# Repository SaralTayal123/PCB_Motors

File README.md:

# PCB_Motors
Code &amp; Firmware to generate continuous coil PCB motor designs

Bare PCB Pictures: 

Completed Dual PCB Stator, center rotor motor

## Media

Videos of the motor spinning and build pictures are in the Media folder

## Cloning the repo
Note that if you clone the repo, you will also need to intialize the submodules. You can do so as follows

```
git clone git@github.com:SaralTayal123/PCB_Motors.git
cd PCB_Motors

git submodule init
git submodule update
```

You will also need to delete/comment out line 6 of `kicad-coil-plugins/pcb_json.py` as follows

```
import json
import pandas as pd
import numpy as np
import matplotlib.pyplot as plt

# from helpers import rotate ### Modify by commenting out ###
```

## How to build your own motors

Option 1 *(Suggested)*: Simply use the existing kicad design and order the current designed version through a manufacturer like PCBway.

Option 2: Design your own PCB motors using the python script. Steps for that are outlined below

### Step 1: 
 
Calculate the appropriate winding pattern. Using the following link, find a slot-magnet combo that will produce a repeating pattern of "A", "B", "C". The ABC phases can be in any order and any case (upper or lower) as long as the pattern that they appear in are consistant. The other restriction is that your Slot number needs to be a multiple of 6 given this winding pattern. For example, I used a 36 slot, 12 magnet pole design and achieved a pattern of "AbC" as pictured below. The upper/lower case refers to the polarity of the coil phase and can be easily switched during wiring, which is why it's not case sensitive as long as the pattern is repeated. 

Calculator link: https://www.bavaria-direct.co.za/scheme/calculator/

This step can be a little tedious since you will need to find magnets that will fit your motor inner/outer diameter while matching the pole pole pair count. If you need more flexibility on not requiring slots be a multiple of 6, or follow a different winding pattern, then this wave motor design isn't the best option for you, and a traditional repeated coil design like this is ideal for you: https://github.com/atomic14/kicad-coil-plugins/tree/216a77b6a4d9532b090e98a6620eb1c3f18db77d

### Step 2: Use the python script

Using the slot/pole combo from step 1 (or using the reccomended 36/12 design), open the continous_coil_gen.ipynb python notebook. Here, input the inner and outer diameter of your coils. You should tailor these to be the width of your magnets to make your motor as effective aas possible. You can also tune a few PCB trace parameters here depending on the capabilities of the PCB manufacturing available to you

### Step 3: Import the Kicad coil design into Kicad

Using the [tool here](https://github.com/atomic14/kicad-coil-plugins/tree/216a77b6a4d9532b090e98a6620eb1c3f18db77d), import your coil design into kicad. If you decide to work with my example board design in KiCad, you should right click the imported coil and move it to the origin to center it perfectly for your design.

Finally, integrate your coils with the rest of the motor controller circuitry to create your own PCB Motor!

## BOM for the example motor
Simple BOM, Cost is ~$25 + shipping
PCBWAY cost ~$26 for 5 boards + Shipping
Magnets 24 pieces @ $0.37 each = $30 (I recommend some spares as they tend to snap/break if they fly out of your hand into a metal object) : https://www.magnet4less.com/neodymium-bar-magnets-1-2-in-x-1-4-in-x-1-8-in-n42

### Rough Specs

Configuration: 2 sided PCB Stator, Rotor in the middle, 8V, Star wiring pattern

Stall torque: 0.008 Nm
Top Speed: 170 Rad/s
Max Power draw: 5 Watts
Peak output power (measured torque x angular velocity): 0.3 Watts

### Testing

Motor charecterization was performed by using 3d printed disc with bolts to serve as a known inertial load to our motor. Measuring the angular acceleration at a full torque command at each angular velocity allowed us to charecterize the torque curve of the motor and the output power curve for the motor (pictured above). This sort of testing is commonnly used for testing cars and is called an inertial dyno. The extra inertial load attached to the PCB motor is pictured below.

The neat thing about using this test is that all one needed to do was add some extra data-logging firmware, and the PCB motors can self-charecterize themselves without any external equipment!

We were also able to monitor a DC Amp-meter on the input power line of the motor to measure system efficiency, howerver there was a lot of switching noise on that power rail to measure a clean signal. Noisy graph is available in Media/torq_eff.png image. The efficiency test needs to be repeated with a low pass filter and a secondary means to test the motor with the motor controller out of the loop. 

### TODO: 
* Why this design
* Star vs Delta wiring
* How to pick winding factor and why conventional winding table won't work

Motor winding image credits: 
https://www.bavaria-direct.co.za/info/#prettyPhoto

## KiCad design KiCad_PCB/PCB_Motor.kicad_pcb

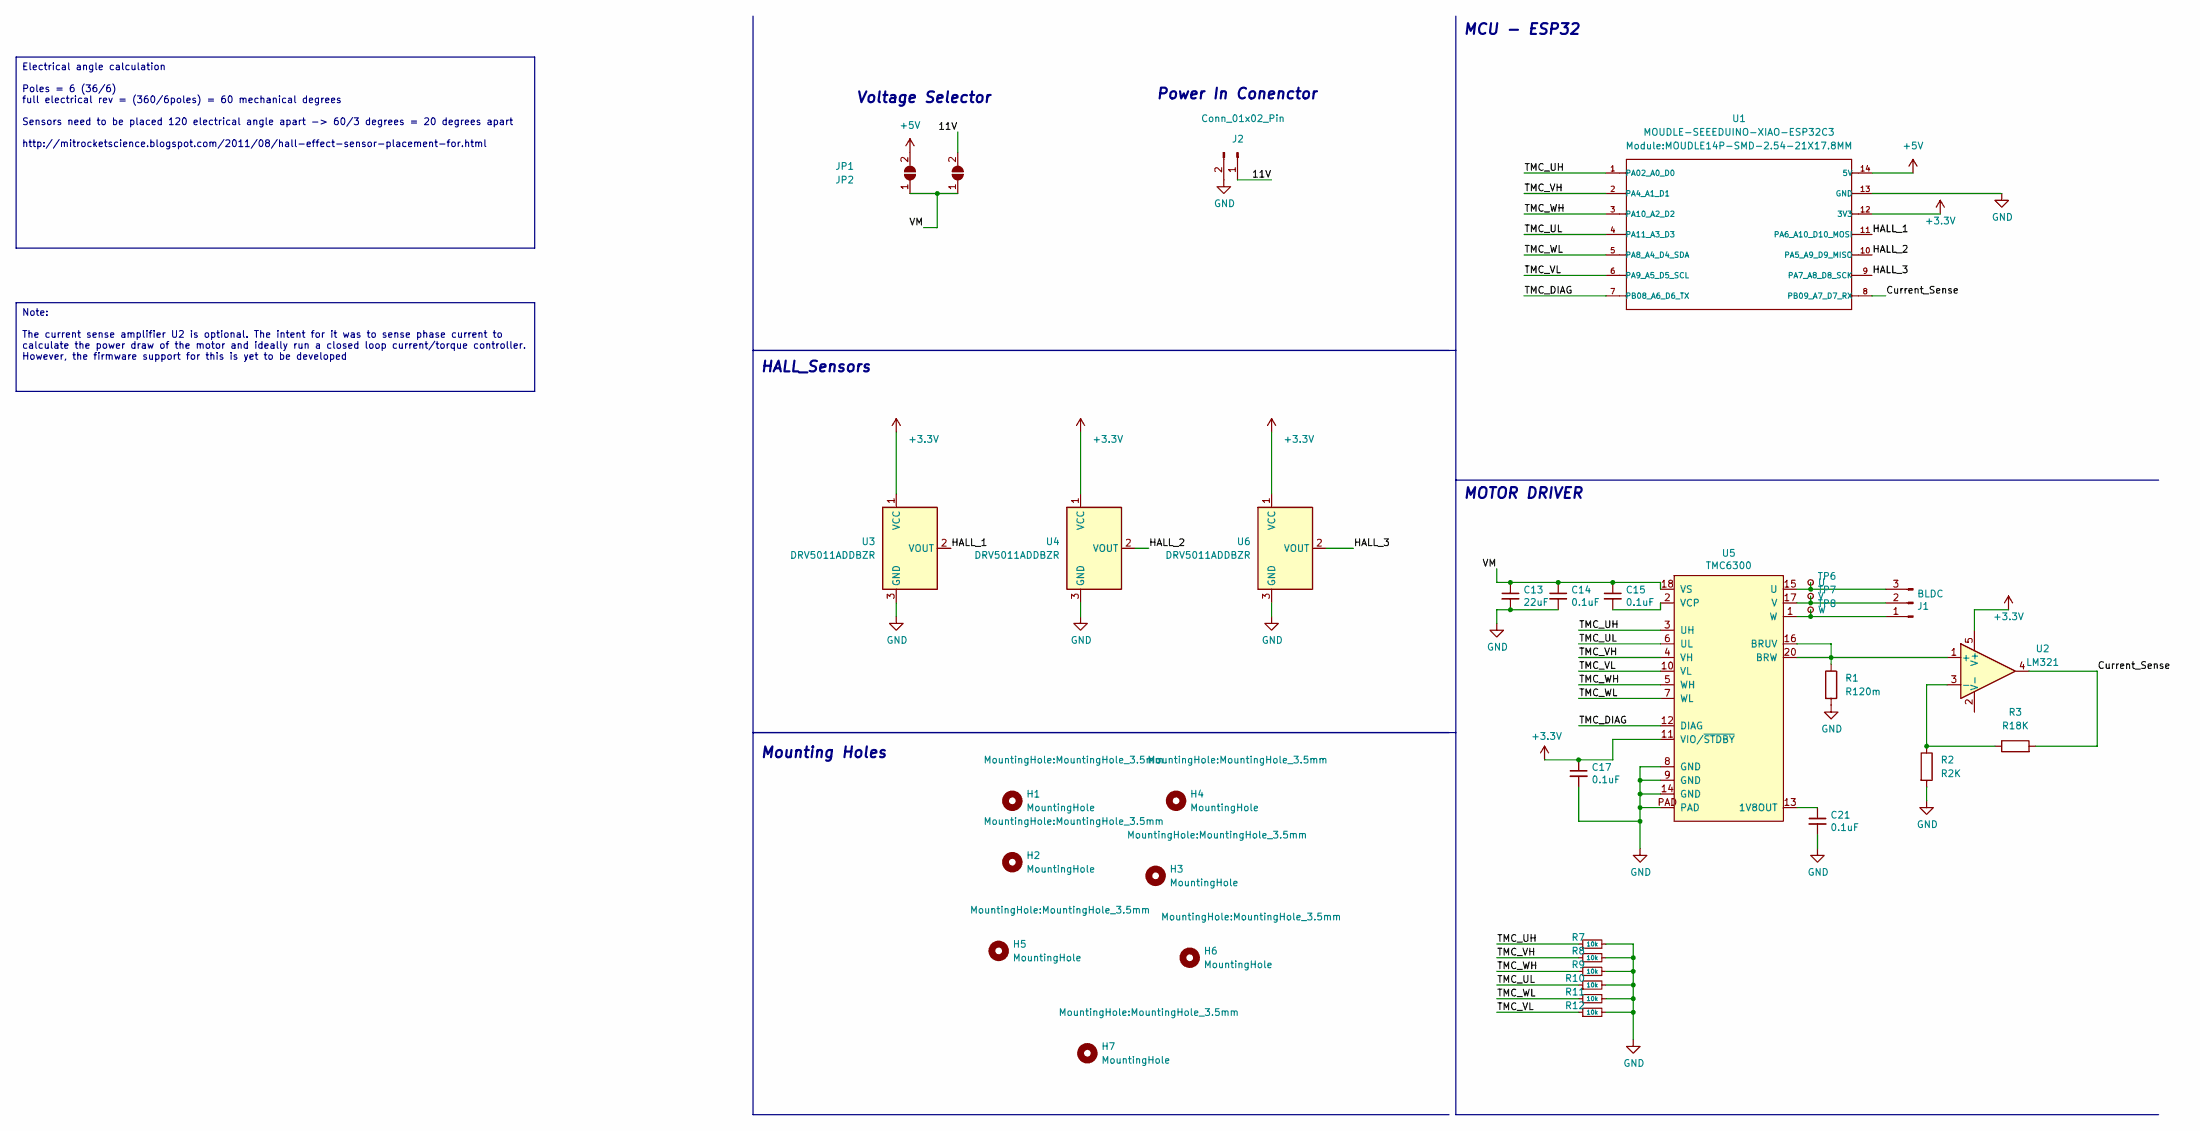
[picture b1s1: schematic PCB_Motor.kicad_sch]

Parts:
C13: 22uF; C_0805_2012Metric; LCSC C98190
C14, C15, C17, C21: 0.1uF; C_0603_1608Metric; LCSC C1591
H1, H2, H3, H4, H5, H6, H7: MountingHole; MountingHole_3.5mm
J1: BLDC; 532610371; LCSC C293630
J2: Conn_01x02_Pin; PinHeader_1x02_P2.54mm_Vertical
JP1, JP2: SolderJumper_2_Open; SolderJumper-2_P1.3mm_Open_TrianglePad1.0x1.5mm
R1: R120m; R_1206_3216Metric
R2: R2K; R_0603_1608Metric
R3: R18K; R_0603_1608Metric
R7, R8, R9, R10, R11, R12: 10k; R_0603_1608Metric; LCSC C98220
TP6: U; TestPoint_Pad_D2.0mm_ValueSilk
TP7: V; TestPoint_Pad_D2.0mm_ValueSilk
TP8: W; TestPoint_Pad_D2.0mm_ValueSilk
U1: MOUDLE-SEEEDUINO-XIAO-ESP32C3; MOUDLE14P-SMD-2.54-21X17.8MM
U2: LM321; SOT-23-5
U3, U4, U6: DRV5011ADDBZR; SOT-23W
U5: TMC6300; QFN-20-1EP_3x3mm_P0.4mm_EP1.65x1.65mm_ThermalVias_LargerVia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; Digikey TMC6300-LA-T

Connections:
+3V3: C17.1, U1.12 (3V3), U2.5 (V+), U3.1 (VCC), U4.1 (VCC), U5.11 (VIO/~STDBY), U6.1 (VCC)
+5V: JP1.2 (B), U1.14 (5V)
/11V: J2.1, JP2.2 (B)
/Current_Sense: R3.2, U1.8 (PB09_A7_D7_RX), U2.4
/HALL_1: U1.11 (PA6_A10_D10_MOSI), U3.2 (VOUT)
/HALL_2: U1.10 (PA5_A9_D9_MISO), U4.2 (VOUT)
/HALL_3: U1.9 (PA7_A8_D8_SCK), U6.2 (VOUT)
/TMC_DIAG: U1.7 (PB08_A6_D6_TX), U5.12 (DIAG)
/TMC_UH: R7.1, U1.1 (PA02_A0_D0), U5.3 (UH)
/TMC_UL: R10.1, U1.4 (PA11_A3_D3), U5.6 (UL)
/TMC_VH: R8.1, U1.2 (PA4_A1_D1), U5.4 (VH)
/TMC_VL: R12.1, U1.6 (PA9_A5_D5_SCL), U5.10 (VL)
/TMC_WH: R9.1, U1.3 (PA10_A2_D2), U5.5 (WH)
/TMC_WL: R11.1, U1.5 (PA8_A4_D4_SDA), U5.7 (WL)
/VM: C13.1, C14.1, C15.1, JP1.1 (A), JP2.1 (A), U5.18 (VS)
GND: C13.2, C14.2, C17.2, C21.2, J2.2, R1.2, R2.2, R7.2, R8.2, R9.2, R10.2, R11.2, R12.2, U1.13 (GND), U3.3 (GND), U4.3 (GND), U5.8 (GND), U5.9 (GND), U5.14 (GND), U5.PAD, U6.3 (GND)
unnamed: J1.1, TP8.1, U5.1 (W)
unnamed: J1.2, TP7.1, U5.17 (V)
unnamed: J1.3, TP6.1, U5.15 (U)
unnamed: R1.1, U2.1 (+), U5.16 (BRUV), U5.20 (BRW)
unnamed: R2.1, R3.1, U2.3 (-)
unnamed: C21.1, U5.13 (1V8OUT)
unnamed: C15.2, U5.2 (VCP)

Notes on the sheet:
Note: The current sense amplifier U2 is optional. The intent for it was to sense phase current to calculate the power draw of the motor and ideally run a closed loop current/torque controller. However, the firmware support for this is yet to be developed
Electrical angle calculation Poles = 6 (36/6) full electrical rev = (360/6poles) = 60 mechanical degrees Sensors need to be placed 120 electrical angle apart -> 60/3 degrees = 20 degrees apart http://mitrocketscience.blogspot.com/2011/08/hall-effect-sensor-placement-for.html
Power In Conenctor
MCU - ESP32
MOTOR DRIVER
Voltage Selector
HALL_Sensors
Mounting Holes

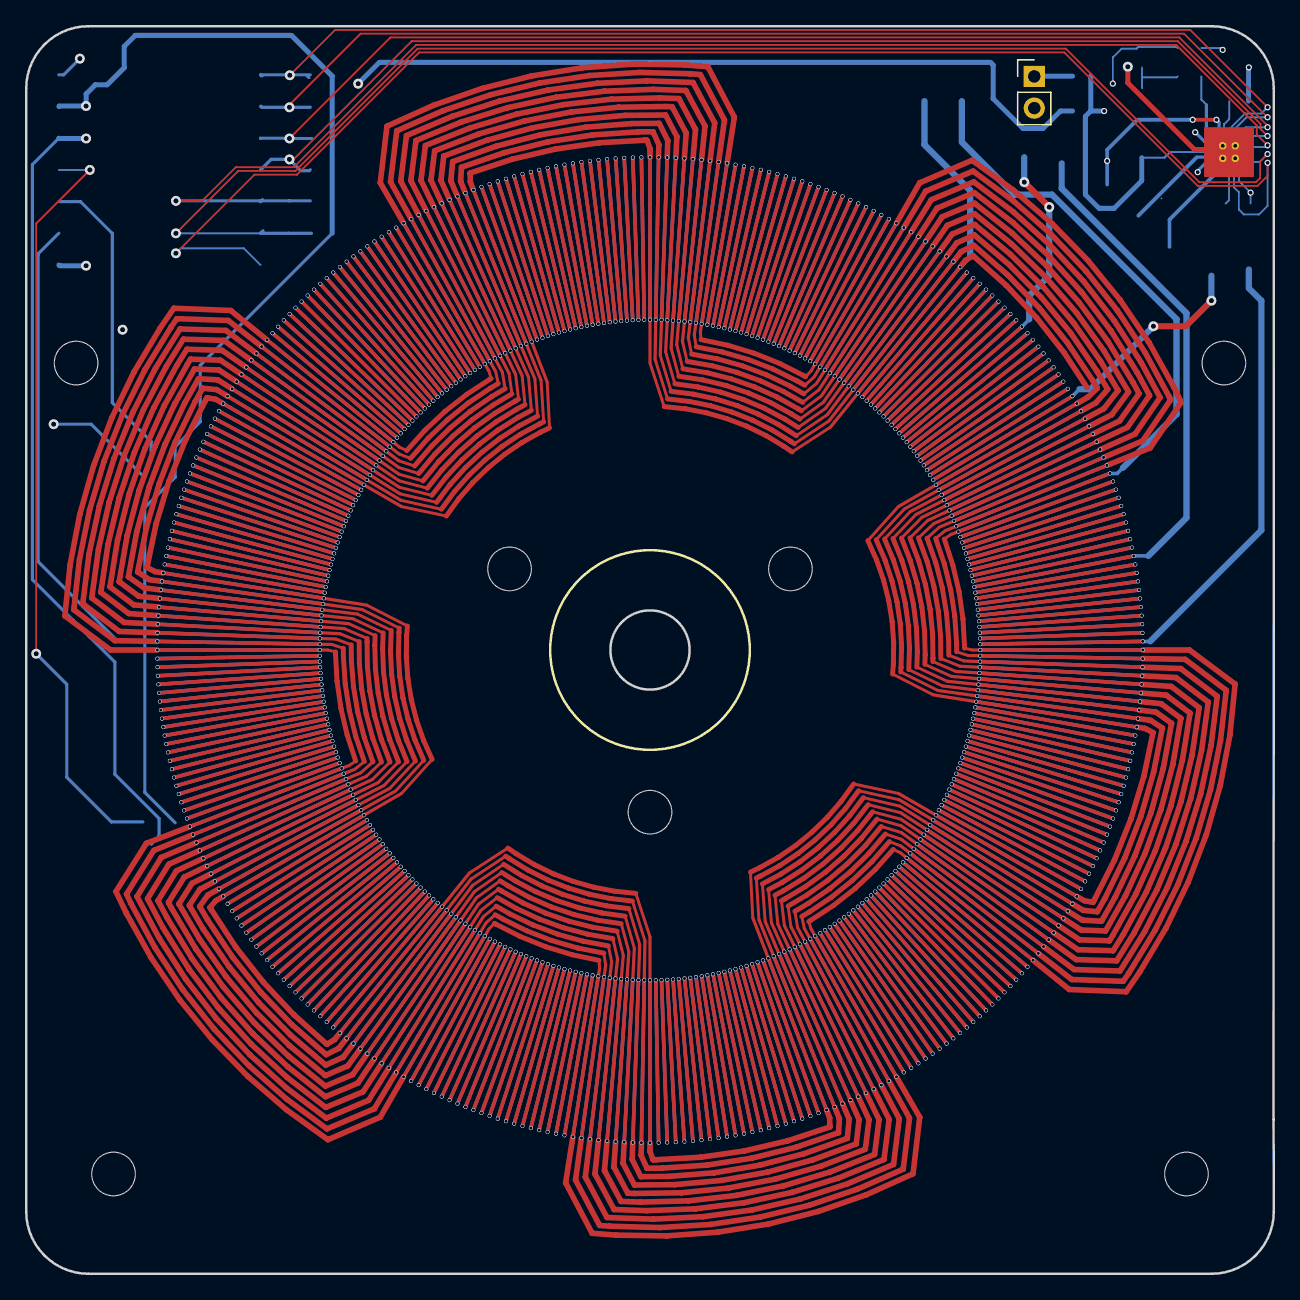
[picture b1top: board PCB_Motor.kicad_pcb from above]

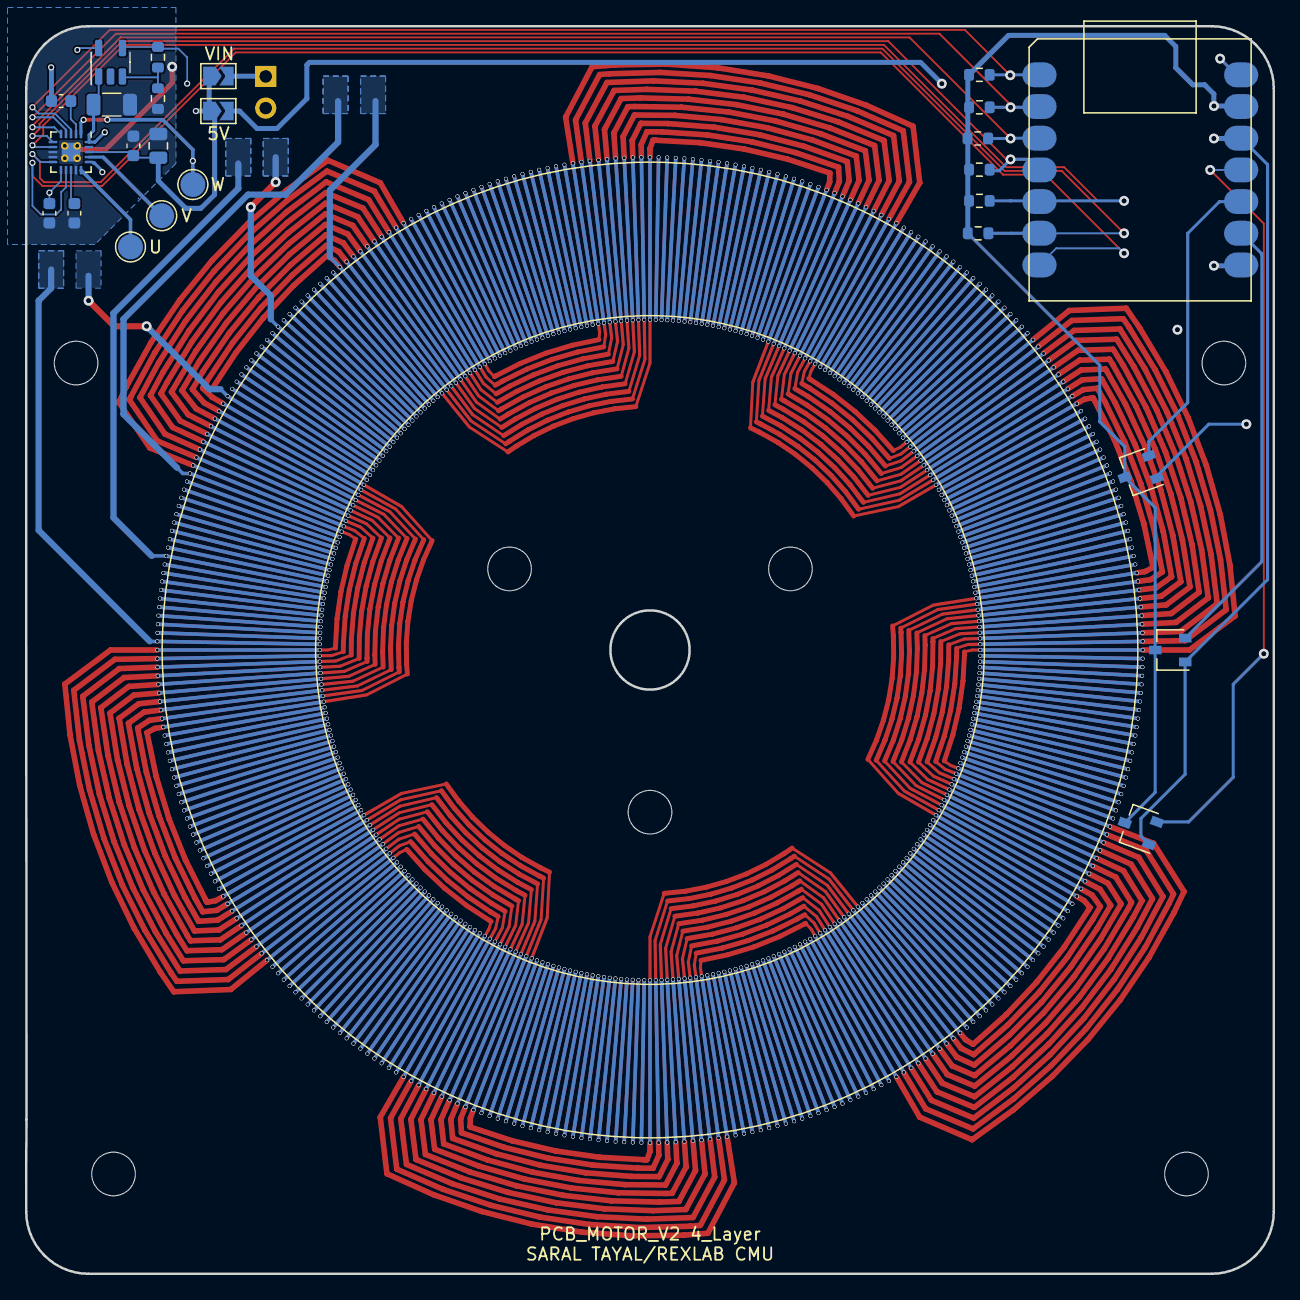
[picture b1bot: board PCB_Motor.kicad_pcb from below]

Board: 4 copper layers, 100.0 x 100.0 mm, 33 parts (25 on the bottom side), 23 nets.

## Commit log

2024-01-17 inital sync commit
2024-01-18 Sync firmware and PCB
2024-01-29 Updated docs
    Media doc
    shrunk video file size
2024-01-29 Pic file typo fix
